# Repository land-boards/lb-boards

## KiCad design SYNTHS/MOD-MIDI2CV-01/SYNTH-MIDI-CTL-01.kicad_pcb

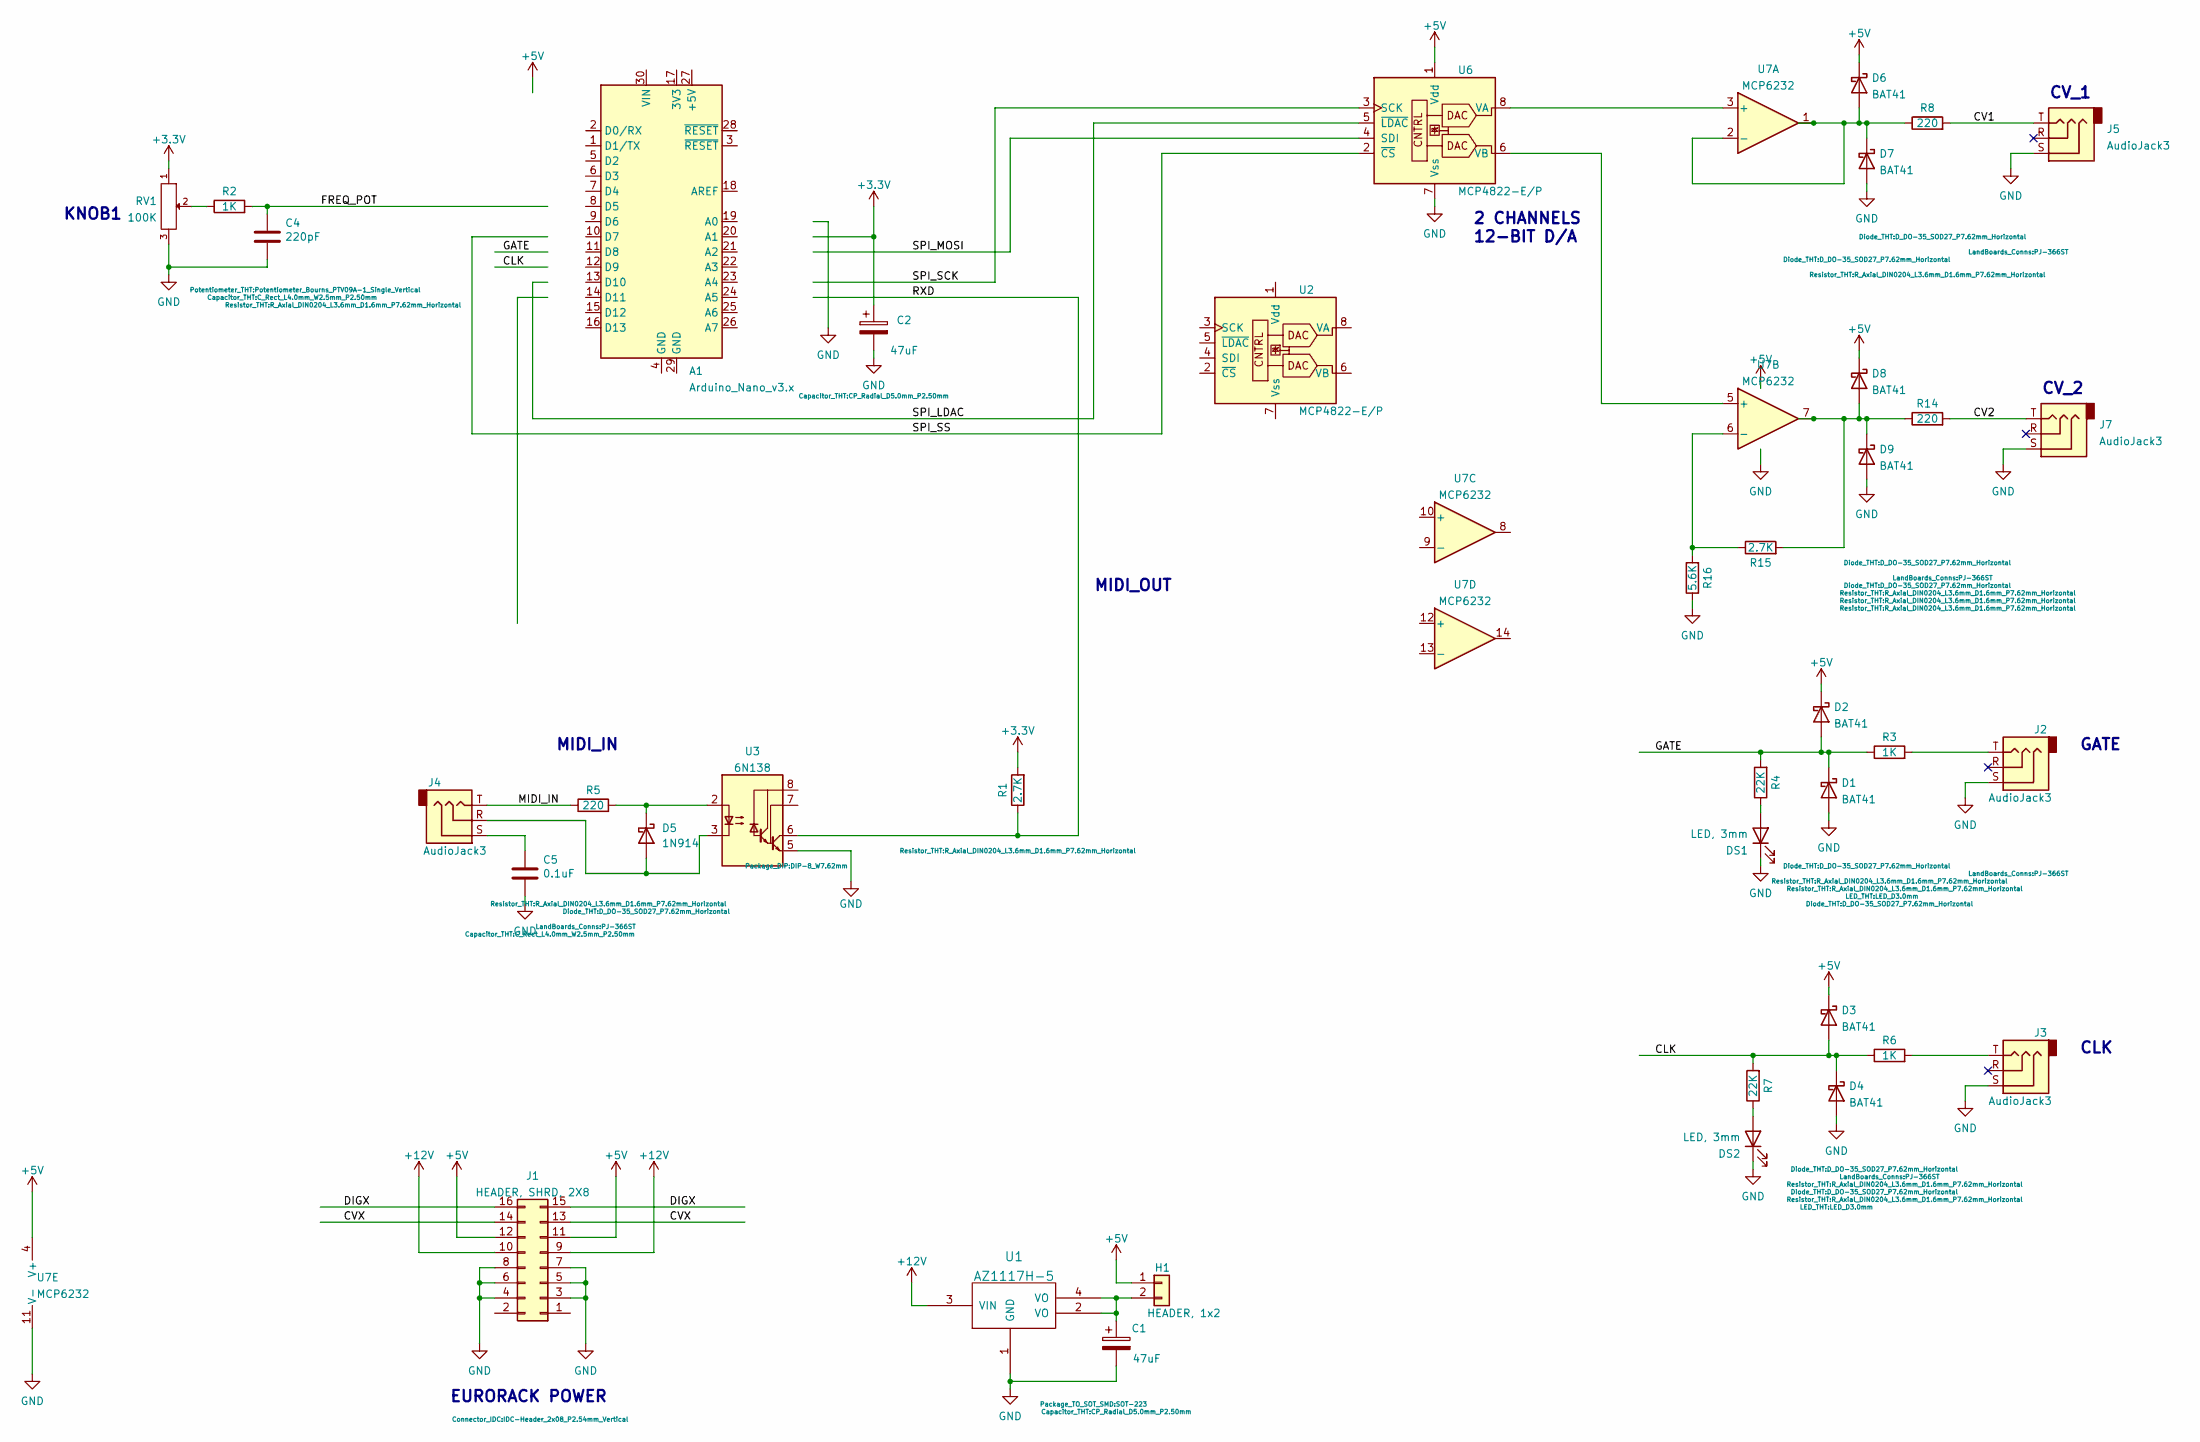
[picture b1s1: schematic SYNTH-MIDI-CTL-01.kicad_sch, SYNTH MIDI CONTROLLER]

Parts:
A1: Arduino_Nano_v3.x; Arduino_Nano
C1, C2: 47uF; CP_Radial_D5.0mm_P2.50mm
C4: 220pF; C_Rect_L4.0mm_W2.5mm_P2.50mm
C5: 0.1uF; C_Rect_L4.0mm_W2.5mm_P2.50mm
D1, D2, D3, D4, D6, D7, D8, D9: BAT41; D_DO-35_SOD27_P7.62mm_Horizontal
D5: 1N914; D_DO-35_SOD27_P7.62mm_Horizontal
DS1, DS2: LED, 3mm; LED_D3.0mm
H1: HEADER, 1x2; PinHeader_1x02_P2.54mm_Vertical
J1: HEADER, SHRD, 2X8; IDC-Header_2x08_P2.54mm_Vertical
J2, J3, J4, J5, J7: AudioJack3; PJ-366ST
R1, R15: 2.7K; R_Axial_DIN0204_L3.6mm_D1.6mm_P7.62mm_Horizontal
R2, R3, R6: 1K; R_Axial_DIN0204_L3.6mm_D1.6mm_P7.62mm_Horizontal
R4, R7: 22K; R_Axial_DIN0204_L3.6mm_D1.6mm_P7.62mm_Horizontal
R5, R8, R14: 220; R_Axial_DIN0204_L3.6mm_D1.6mm_P7.62mm_Horizontal
R16: 5.6K; R_Axial_DIN0204_L3.6mm_D1.6mm_P7.62mm_Horizontal
RV1: 100K; Potentiometer_Bourns_PTV09A-1_Single_Vertical
U1: AZ1117H-5; SOT-223
U2, U6: MCP4822-E/P; DIP-8_W7.62mm
U3: 6N138; DIP-8_W7.62mm
U7: MCP6232; DIP-14_W7.62mm_Socket_LongPads

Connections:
+3V3: C2.1, R1.2, RV1.1
+5V: D2.1 (K), D3.1 (K), D6.1 (K), D8.1 (K), H1.1, J1.11, J1.12, U6.1 (Vdd), U7.4 (V+)
+12V: J1.9, J1.10, U1.3 (VIN)
/CLK: D3.2 (A), D4.1 (K), R6.1, R7.2
/CV1: J5.T, R8.2
/CV2: J7.T, R14.2
/CVX: J1.13, J1.14
/DIGX: J1.15, J1.16
/FREQ_POT: C4.1, R2.2
/GATE: D1.1 (K), D2.2 (A), R3.1, R4.2
/MIDI_IN: J4.T, R5.1
/RXD: R1.1, U3.6 (VO2)
/SPI_LDAC: U6.5 (~LDAC)
/SPI_MOSI: U6.4 (SDI)
/SPI_SCK: U6.3 (SCK)
/SPI_SS: U6.2 (~CS)
GND: C1.2, C2.2, C4.2, C5.2, D1.2 (A), D4.2 (A), D7.2 (A), D9.2 (A), DS1.1 (K), DS2.1 (K), J1.3, J1.4, J1.5, J1.6, J1.7, J1.8, J2.S, J3.S, J5.S, J7.S, R16.1, RV1.3, U1.1 (GND), U3.5 (GND), U6.7 (Vss), U7.11 (V-)
unnamed: C1.1, H1.2, U1.2 (VO), U1.4 (VO)
unnamed: C5.1, J4.S
unnamed: D5.1 (K), R5.2, U3.2 (C1)
unnamed: D5.2 (A), J4.R, U3.3 (C2)
unnamed: D6.2 (A), D7.1 (K), R8.1, U7.1, U7.2 (-)
unnamed: D8.2 (A), D9.1 (K), R14.1, R15.2, U7.7
unnamed: DS1.2 (A), R4.1
unnamed: DS2.2 (A), R7.1
unnamed: J2.T, R3.2
unnamed: J3.T, R6.2
unnamed: R2.1, RV1.2
unnamed: R15.1, R16.2, U7.6 (-)
unnamed: U6.6 (VB), U7.5 (+)
unnamed: U6.8 (VA), U7.3 (+)

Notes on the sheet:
CV_2
GATE
MIDI_IN
2 CHANNELS 12-BIT D/A
KNOB1
MIDI_OUT
CLK
CV_1
EURORACK POWER

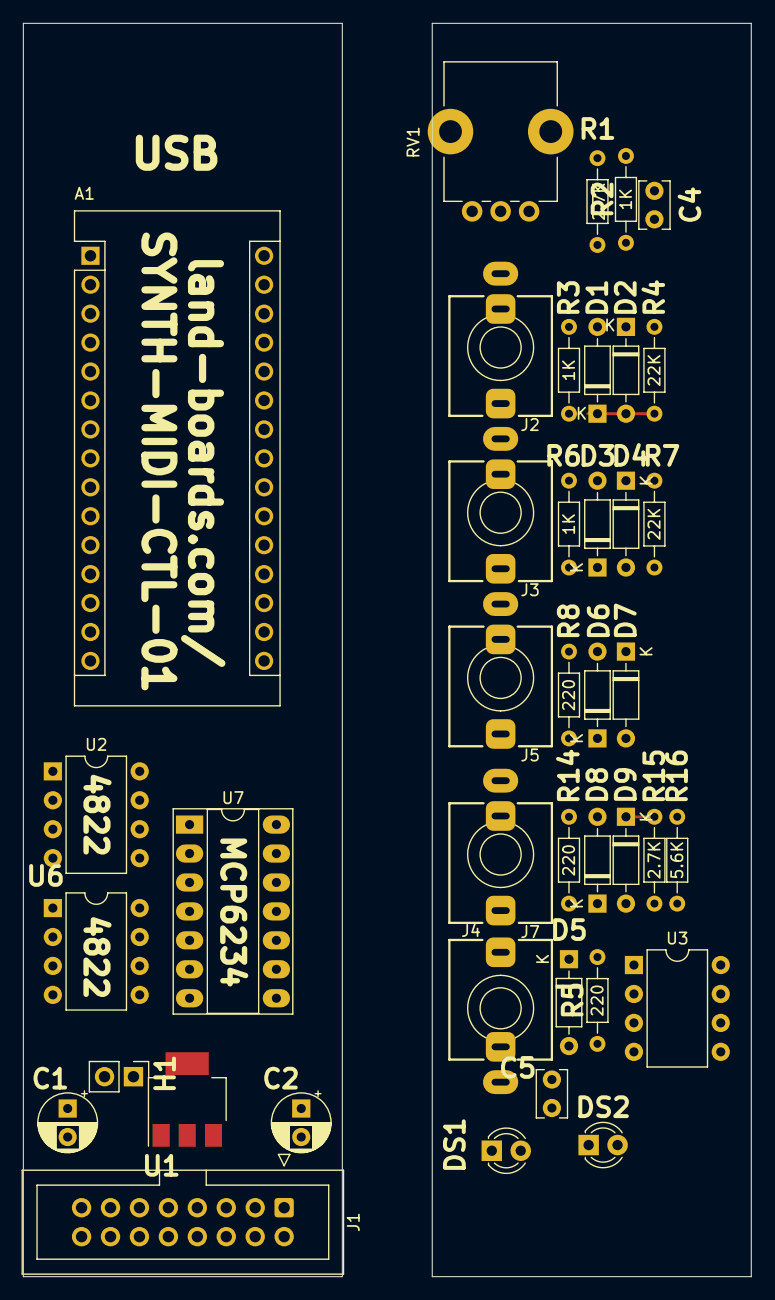
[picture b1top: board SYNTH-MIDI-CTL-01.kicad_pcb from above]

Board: 2 copper layers, 63.9 x 110.0 mm, 40 parts (0 on the bottom side), 27 nets.

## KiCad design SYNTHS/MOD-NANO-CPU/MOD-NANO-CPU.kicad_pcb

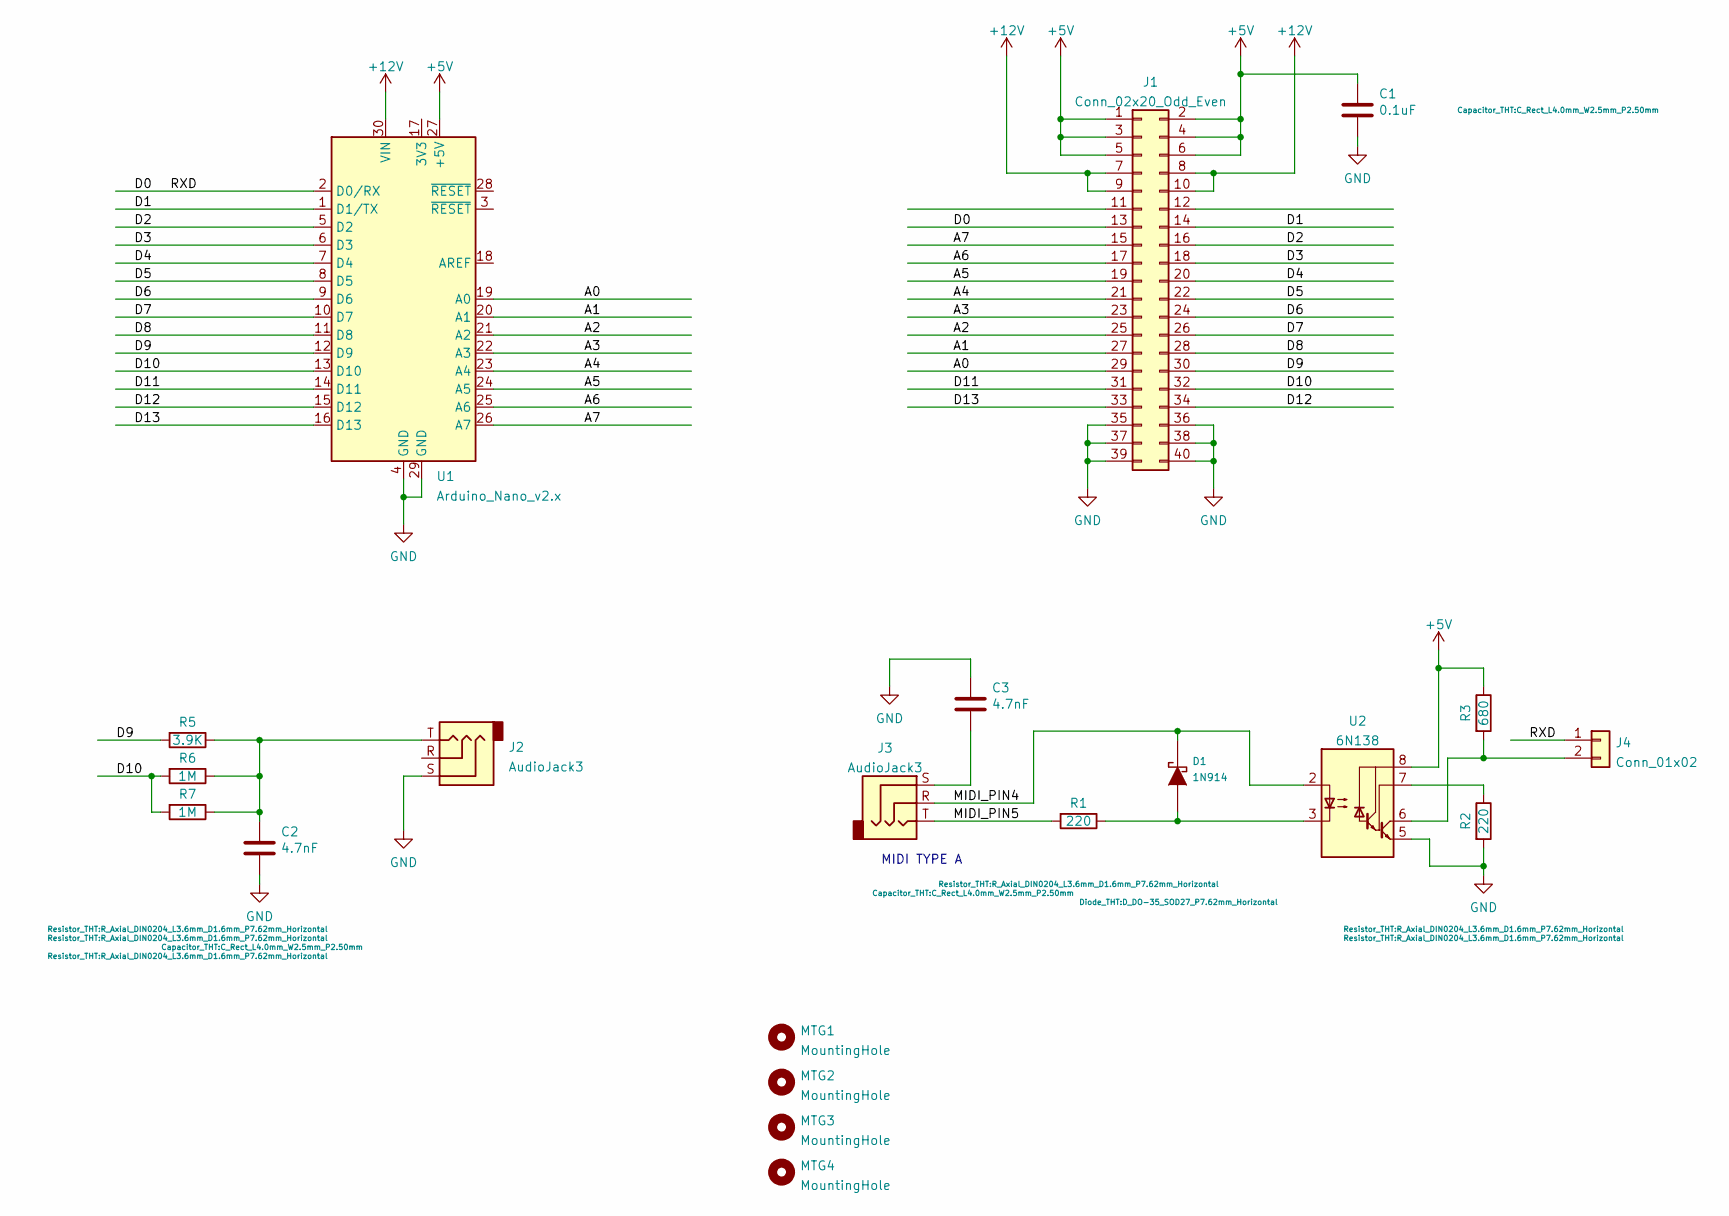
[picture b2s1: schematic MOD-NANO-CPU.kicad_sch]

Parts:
C1: 0.1uF; C_Rect_L4.0mm_W2.5mm_P2.50mm
C2, C3: 4.7nF; C_Rect_L4.0mm_W2.5mm_P2.50mm
D1: 1N914; D_DO-35_SOD27_P7.62mm_Horizontal
J1: Conn_02x20_Odd_Even; PinHeader_2x20_P2.54mm_Vertical
J2, J3: AudioJack3; Jack_3.5mm_CUI_SJ1-3523N_Horizontal
J4: Conn_01x02; PinHeader_1x02_P2.54mm_Vertical
MTG1, MTG2, MTG3, MTG4: MountingHole; MTG-4-40
R1, R2: 220; R_Axial_DIN0204_L3.6mm_D1.6mm_P7.62mm_Horizontal
R3: 680; R_Axial_DIN0204_L3.6mm_D1.6mm_P7.62mm_Horizontal
R5: 3.9K; R_Axial_DIN0204_L3.6mm_D1.6mm_P7.62mm_Horizontal
R6, R7: 1M; R_Axial_DIN0204_L3.6mm_D1.6mm_P7.62mm_Horizontal
U1: Arduino_Nano_v2.x; Arduino_Nano
U2: 6N138; DIP-8_W7.62mm_Socket_LongPads

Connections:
+5V: C1.1, J1.1, J1.2, J1.3, J1.4, J1.5, J1.6, R3.1, U1.27 (+5V), U2.8 (VCC)
+12V: J1.7, J1.8, J1.9, J1.10, U1.30 (VIN)
/A0: J1.29, U1.19 (A0)
/A1: J1.27, U1.20 (A1)
/A2: J1.25, U1.21 (A2)
/A3: J1.23, U1.22 (A3)
/A4: J1.21, U1.23 (A4)
/A5: J1.19, U1.24 (A5)
/A6: J1.17, U1.25 (A6)
/A7: J1.15, U1.26 (A7)
/D0: J1.13, J4.1, U1.2 (D0/RX)
/D1: J1.14, U1.1 (D1/TX)
/D2: J1.16, U1.5 (D2)
/D3: J1.18, U1.6 (D3)
/D4: J1.20, U1.7 (D4)
/D5: J1.22, U1.8 (D5)
/D6: J1.24, U1.9 (D6)
/D7: J1.26, U1.10 (D7)
/D8: J1.28, U1.11 (D8)
/D9: J1.30, R5.2, U1.12 (D9)
/D10: J1.32, R6.2, R7.2, U1.13 (D10)
/D11: J1.31, U1.14 (D11)
/D12: J1.34, U1.15 (D12)
/D13: J1.33, U1.16 (D13)
/MIDI_PIN4: D1.1 (K), J3.R, U2.2 (C1)
/MIDI_PIN5: J3.T, R1.2
GND: C1.2, C2.2, C3.1, J1.35, J1.36, J1.37, J1.38, J1.39, J1.40, J2.S, R2.2, U1.4 (GND), U1.29 (GND), U2.5 (GND)
unnamed: C2.1, J2.T, R5.1, R6.1, R7.1
unnamed: C3.2, J3.S
unnamed: D1.2 (A), R1.1, U2.3 (C2)
unnamed: R2.1, U2.7 (VO1)
unnamed: J4.2, R3.2, U2.6 (VO2)

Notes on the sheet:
MIDI TYPE A

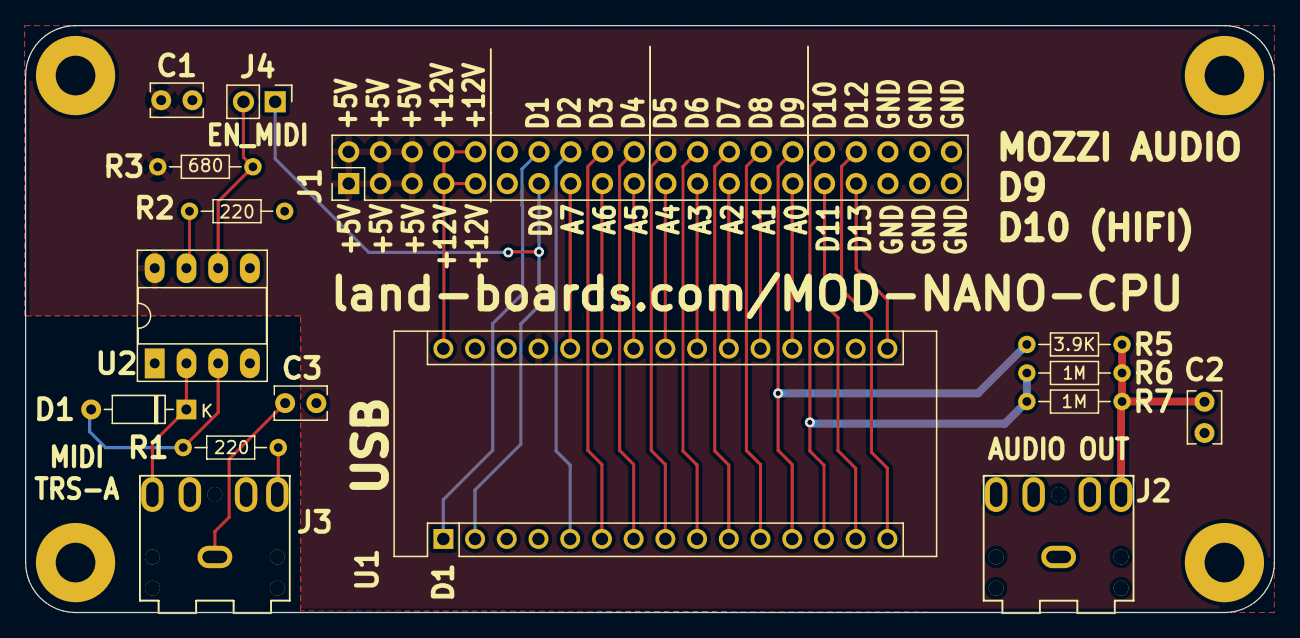
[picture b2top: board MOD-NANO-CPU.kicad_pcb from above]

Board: 2 copper layers, 100.0 x 47.0 mm, 20 parts (0 on the bottom side), 32 nets.

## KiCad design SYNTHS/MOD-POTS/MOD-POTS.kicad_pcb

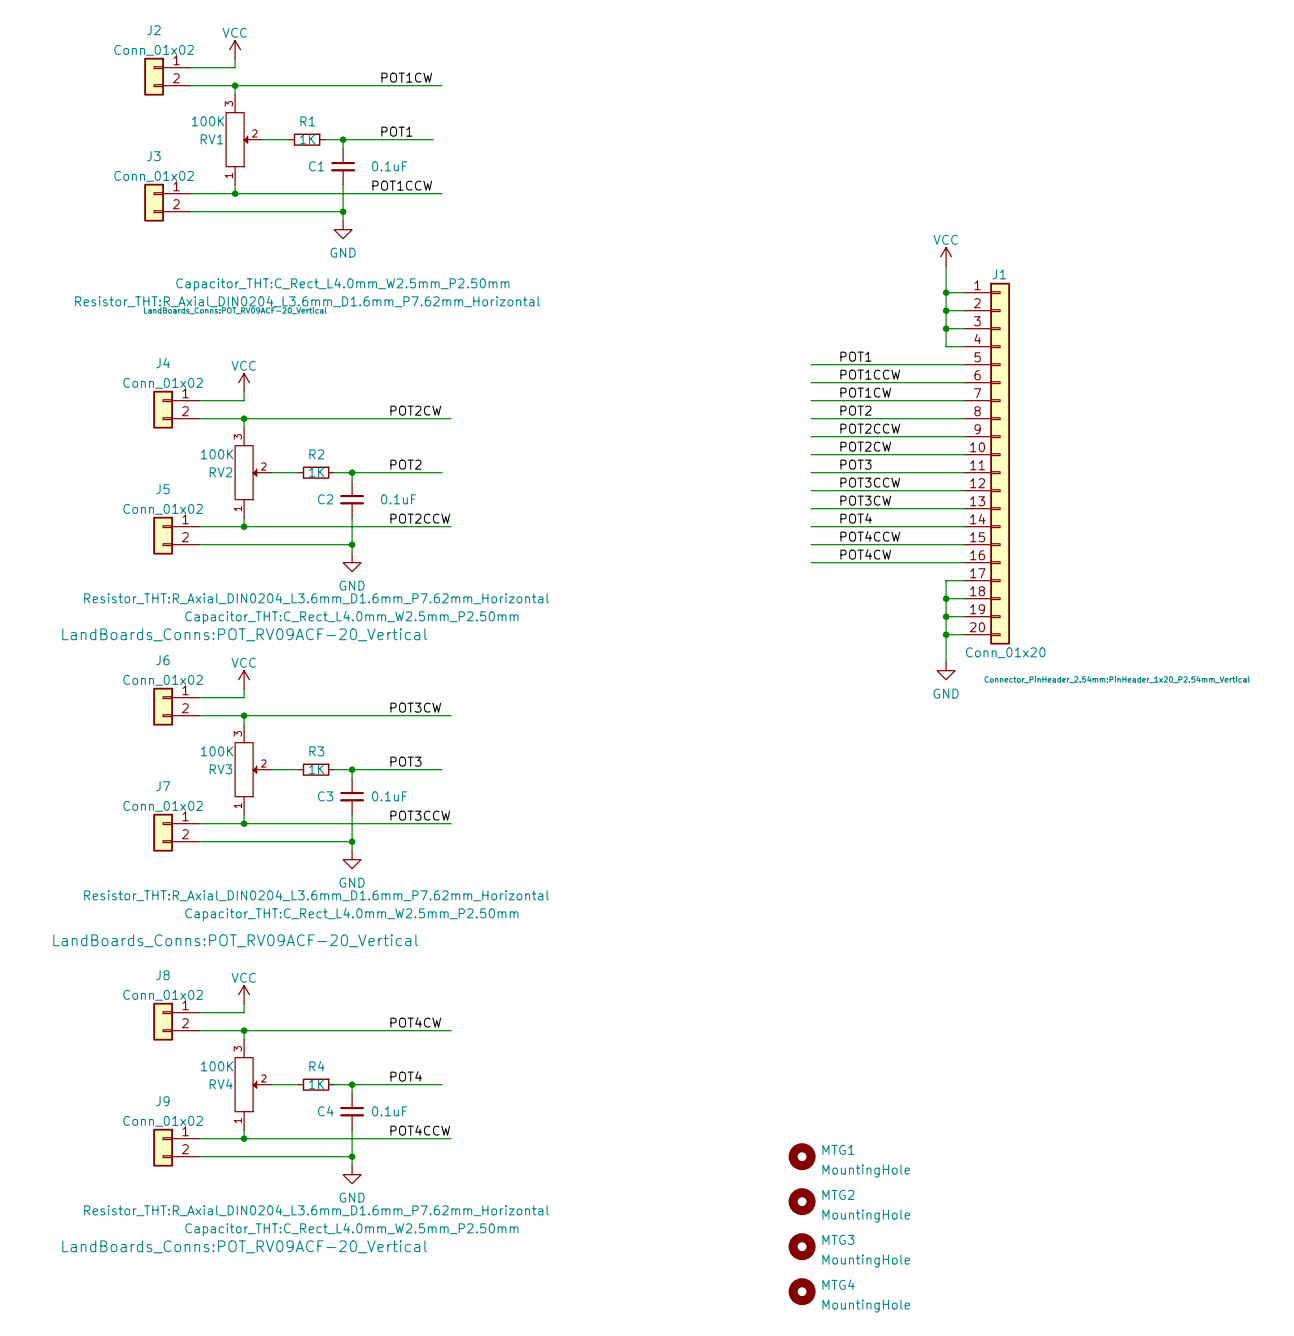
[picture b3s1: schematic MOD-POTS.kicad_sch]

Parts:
C1, C2, C3, C4: 0.1uF; C_Rect_L4.0mm_W2.5mm_P2.50mm
J1: Conn_01x20; PinHeader_1x20_P2.54mm_Vertical
J2, J3, J4, J5, J6, J7, J8, J9: Conn_01x02; PinHeader_1x02_P2.54mm_Vertical
MTG1, MTG2, MTG3, MTG4: MountingHole; MTG-4-40
R1, R2, R3, R4: 1K; R_Axial_DIN0204_L3.6mm_D1.6mm_P7.62mm_Horizontal
RV1, RV2, RV3, RV4: 100K; POT_RV09ACF-20_Vertical

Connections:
/POT1: C1.1, J1.5, R1.1
/POT1CCW: J1.6, J3.1, RV1.1
/POT1CW: J1.7, J2.2, RV1.3
/POT2: C2.1, J1.8, R2.1
/POT2CCW: J1.9, J5.1, RV2.1
/POT2CW: J1.10, J4.2, RV2.3
/POT3: C3.1, J1.11, R3.1
/POT3CCW: J1.12, J7.1, RV3.1
/POT3CW: J1.13, J6.2, RV3.3
/POT4: C4.1, J1.14, R4.1
/POT4CCW: J1.15, J9.1, RV4.1
/POT4CW: J1.16, J8.2, RV4.3
GND: C1.2, C2.2, C3.2, C4.2, J1.17, J1.18, J1.19, J1.20, J3.2, J5.2, J7.2, J9.2
unnamed: R1.2, RV1.2
unnamed: R2.2, RV2.2
unnamed: R3.2, RV3.2
unnamed: R4.2, RV4.2
VCC: J1.1, J1.2, J1.3, J1.4, J2.1, J4.1, J6.1, J8.1

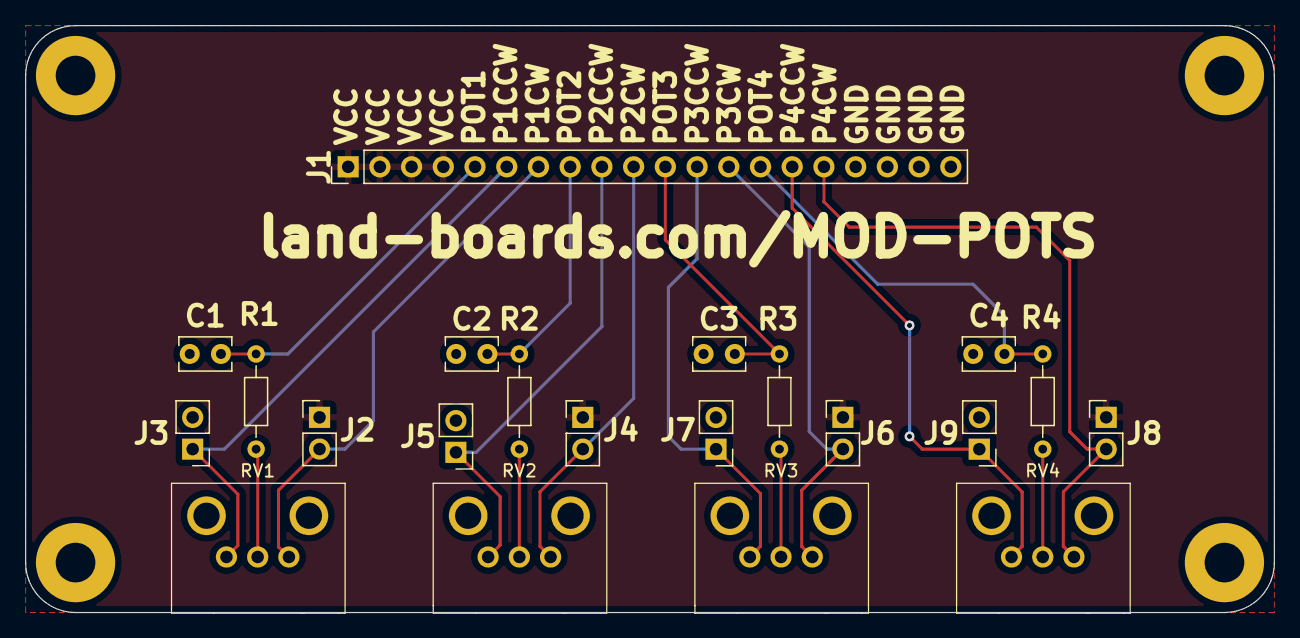
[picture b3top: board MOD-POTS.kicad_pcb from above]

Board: 2 copper layers, 100.0 x 47.0 mm, 25 parts (0 on the bottom side), 18 nets.

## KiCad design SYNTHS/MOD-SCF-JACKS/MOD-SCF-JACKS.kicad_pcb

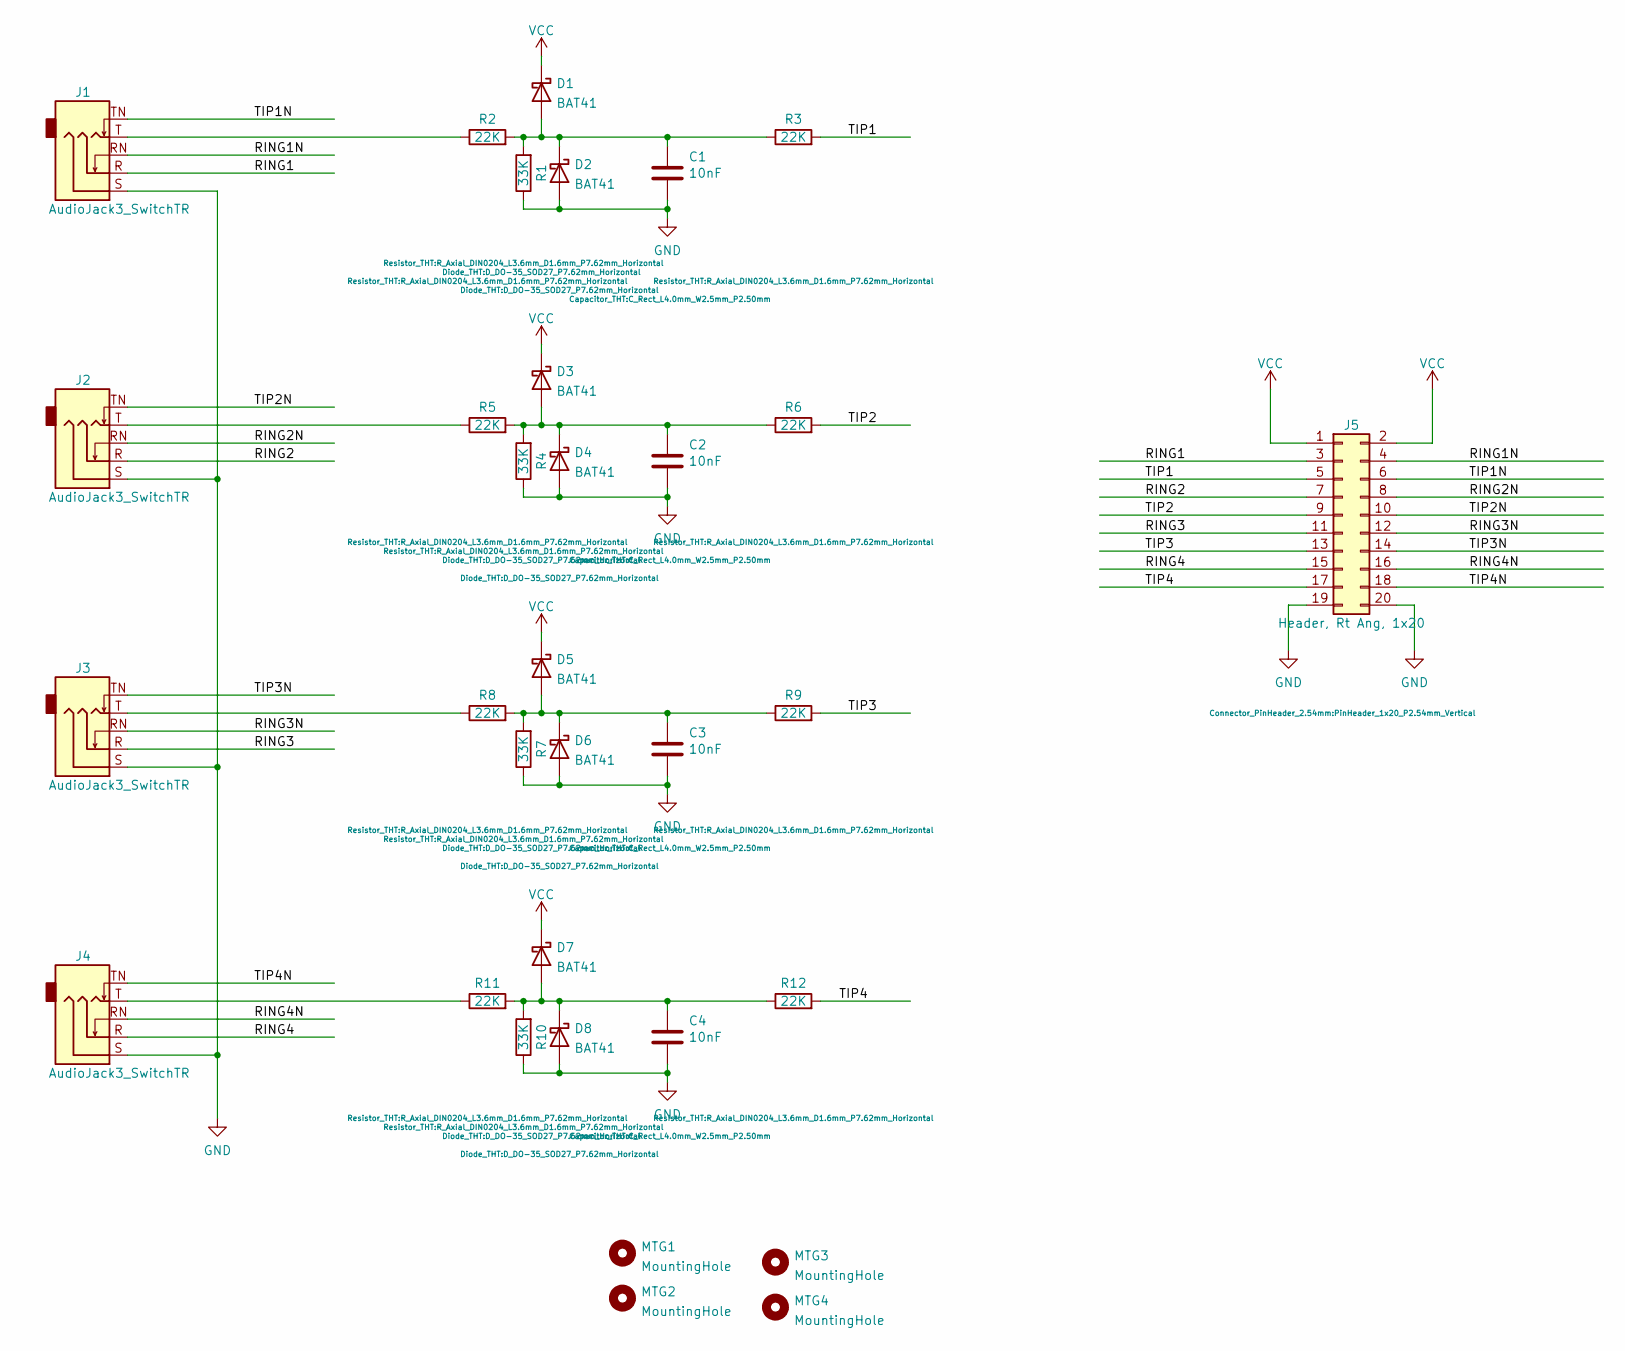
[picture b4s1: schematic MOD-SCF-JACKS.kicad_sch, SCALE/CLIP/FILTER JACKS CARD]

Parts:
C1, C2, C3, C4: 10nF; C_Rect_L4.0mm_W2.5mm_P2.50mm
D1, D2, D3, D4, D5, D6, D7, D8: BAT41; D_DO-35_SOD27_P7.62mm_Horizontal
J1, J2, J3, J4: AudioJack3_SwitchTR; Jack_3.5mm_CUI_SJ1-3523N_Horizontal
J5: Header, Rt Ang, 1x20; PinHeader_1x20_P2.54mm_Vertical
MTG1, MTG2, MTG3, MTG4: MountingHole; MTG-4-40
R1, R4, R7, R10: 33K; R_Axial_DIN0204_L3.6mm_D1.6mm_P7.62mm_Horizontal
R2, R3, R5, R6, R8, R9, R11, R12: 22K; R_Axial_DIN0204_L3.6mm_D1.6mm_P7.62mm_Horizontal

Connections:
/RING1: J1.R, J5.3
/RING1N: J1.RN, J5.4
/RING2: J2.R, J5.7
/RING2N: J2.RN, J5.8
/RING3: J3.R, J5.11
/RING3N: J3.RN, J5.12
/RING4: J4.R, J5.15
/RING4N: J4.RN, J5.16
/TIP1: J5.5, R3.2
/TIP1N: J1.TN, J5.6
/TIP2: J5.9, R6.2
/TIP2N: J2.TN, J5.10
/TIP3: J5.13, R9.2
/TIP3N: J3.TN, J5.14
/TIP4: J5.17, R12.2
/TIP4N: J4.TN, J5.18
GND: C1.2, C2.2, C3.2, C4.2, D2.2 (A), D4.2 (A), D6.2 (A), D8.2 (A), J1.S, J2.S, J3.S, J4.S, J5.19, J5.20, R1.1, R4.1, R7.1, R10.1
unnamed: C1.1, D1.2 (A), D2.1 (K), R1.2, R2.2, R3.1
unnamed: C2.1, D3.2 (A), D4.1 (K), R4.2, R5.2, R6.1
unnamed: C3.1, D5.2 (A), D6.1 (K), R7.2, R8.2, R9.1
unnamed: C4.1, D7.2 (A), D8.1 (K), R10.2, R11.2, R12.1
unnamed: J1.T, R2.1
unnamed: J2.T, R5.1
unnamed: J3.T, R8.1
unnamed: J4.T, R11.1
VCC: D1.1 (K), D3.1 (K), D5.1 (K), D7.1 (K), J5.1, J5.2

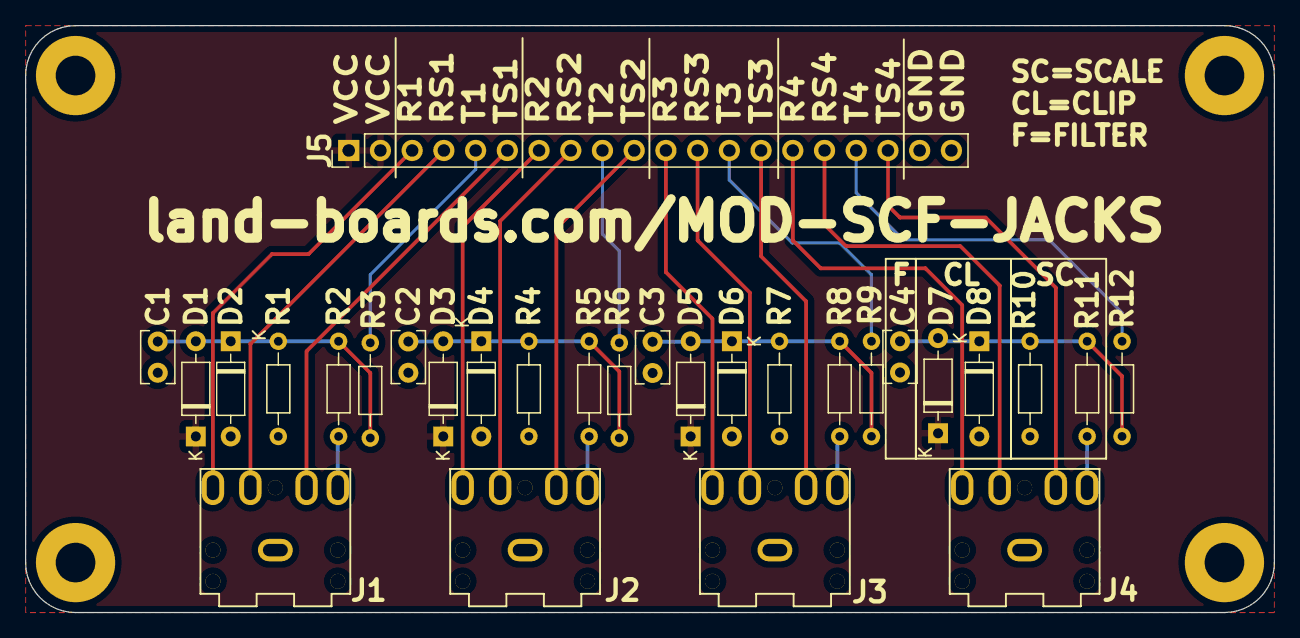
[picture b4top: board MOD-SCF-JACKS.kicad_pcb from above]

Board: 2 copper layers, 100.0 x 47.0 mm, 33 parts (0 on the bottom side), 26 nets.

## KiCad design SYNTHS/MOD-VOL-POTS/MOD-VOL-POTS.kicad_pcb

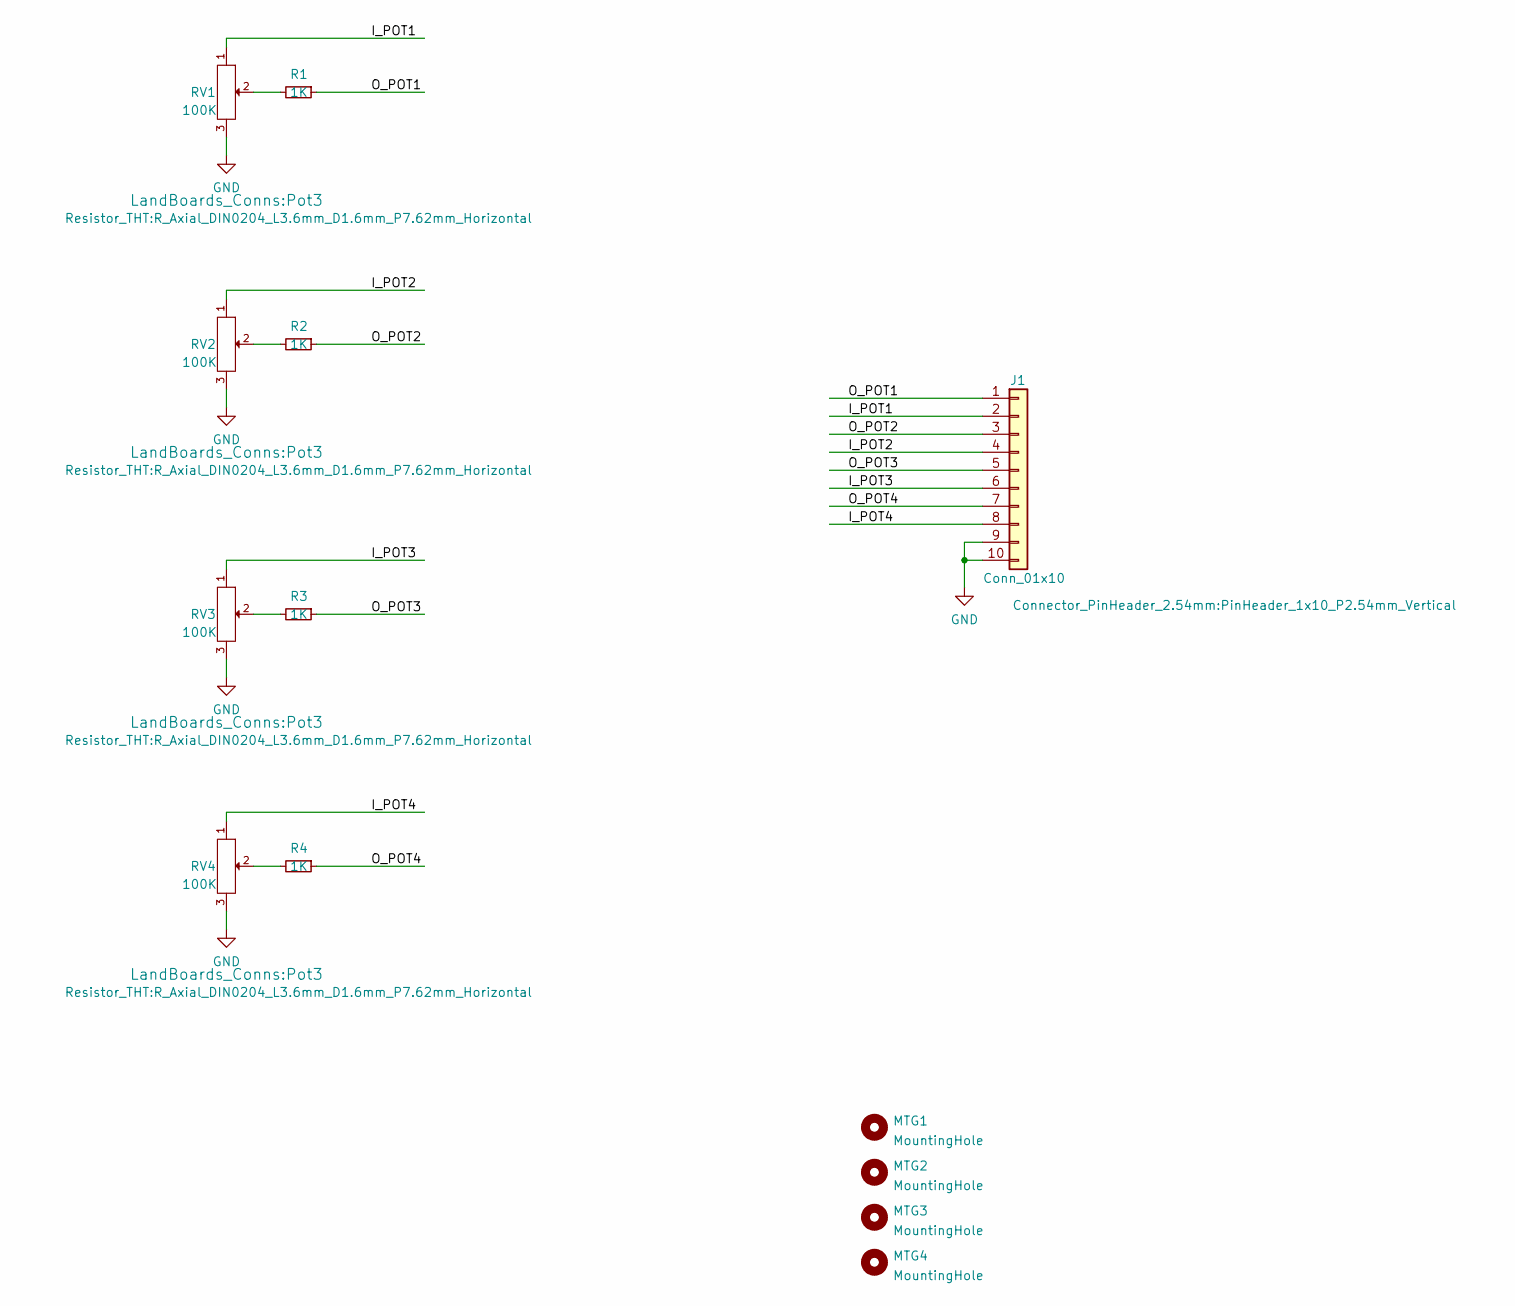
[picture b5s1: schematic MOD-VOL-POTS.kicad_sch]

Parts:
J1: Conn_01x10; PinHeader_1x10_P2.54mm_Vertical
MTG1, MTG2, MTG3, MTG4: MountingHole; MTG-4-40
R1, R2, R3, R4: 1K; R_Axial_DIN0204_L3.6mm_D1.6mm_P7.62mm_Horizontal
RV1, RV2, RV3, RV4: 100K; Pot3

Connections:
/I_POT1: J1.2, RV1.1
/I_POT2: J1.4, RV2.1
/I_POT3: J1.6, RV3.1
/I_POT4: J1.8, RV4.1
/O_POT1: J1.1, R1.1
/O_POT2: J1.3, R2.1
/O_POT3: J1.5, R3.1
/O_POT4: J1.7, R4.1
GND: J1.9, J1.10, RV1.3, RV2.3, RV3.3, RV4.3
unnamed: R1.2, RV1.2
unnamed: R2.2, RV2.2
unnamed: R3.2, RV3.2
unnamed: R4.2, RV4.2

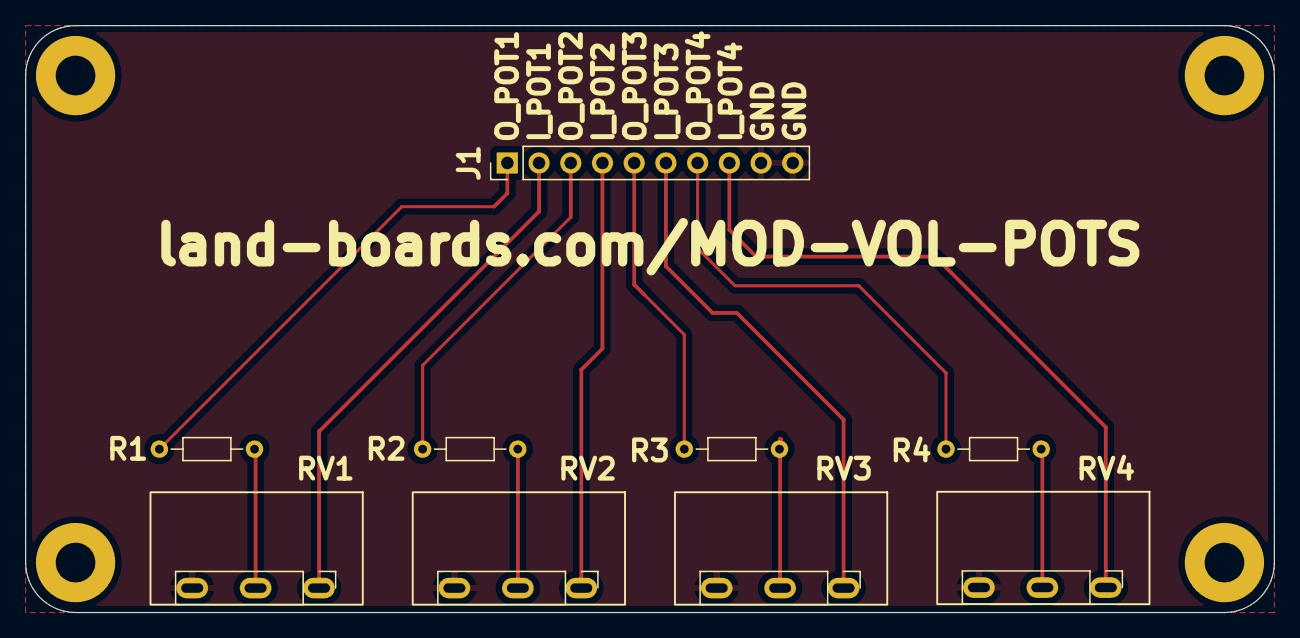
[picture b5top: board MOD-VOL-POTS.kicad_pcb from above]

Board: 2 copper layers, 100.0 x 47.0 mm, 13 parts (0 on the bottom side), 13 nets.
